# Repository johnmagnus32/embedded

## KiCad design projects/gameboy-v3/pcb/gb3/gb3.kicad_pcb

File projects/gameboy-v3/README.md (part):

# gameboy-v3 — Allwinner T113-S3 Linux handheld

**Status:** 🚧 Bring-up. Goal right now: **boot a Linux image on the
[t113-breakout](../t113-breakout) board and get a working serial console.**
Display, sound, and input come later, once Linux boots reliably.

**Build: complete (Steps 0–4 ✅).** All four artifacts + a flashable SD image
(`build/output/gameboy-v3-sd.img`) build reproducibly via `make image` through the
shared engine [`forge/`](../../forge/) (see the [boot matrix](#boot-matrix--interchangeable-components--silicon-results)
for the provider matrix). **Runs on real T113 silicon** — both the custom and
all-OSS stacks boot to an interactive shell (flashing: [first boot](#flashing--first-boot-generic--local-bench)).

## Contents

This is the single doc for the product. Major sections:

- **Overview & build** — [what this is](#what-this-is) · [boot chain](#boot-chain-phase-1-everything-on-microsd) · [build plan (Steps 0–4)](#build-plan--build-it-by-hand-once-then-buildroot) · [UART console](#uart-console) · [both cores (SMP)](#both-cores-smp) · [references](#references)
- **[Boot matrix](#boot-matrix--interchangeable-components--silicon-results)** — the provider-interchange matrix + on-silicon results (formerly BOOT-MATRIX.md).
- **[SPI-NOR layout](#spi-nor-layout--the-loader-contract)** — the loader contract: NOR offsets, GV3NOR1 table, DRAM load addrs (formerly NOR-LAYOUT.md).
- **[Flashing & first boot](#flashing--first-boot-generic--local-bench)** — dd a card, wire the console, expected boot, troubleshooting (formerly FLASH.md).
- **[Remote rig](#remote-bring-up-rig-ssh-driven-nuc)** — the SSH/NUC bring-up runbook: power-cycle, UART capture, FEL (formerly REMOTE-RIG.md).
- **[ILI9341 LCD](#ili9341-spi-lcd-later-phase)** — the SPI display peripheral (formerly LCD-ILI9341.md).

## What this is

The third iteration of the handheld. Where v1 was bare-metal STM32 and v2 was
STM32 + iCE40 FPGA, **v3 moves to a full Linux SBC**: the dual-core ARM
Cortex-A7 **Allwinner T113-S3** (with 128 MB in-package DDR3) running mainline
Linux. Game logic, display, and audio all run as Linux userspace/kernel on the
one SoC — no separate CPU/PPU split.

For Phase 1 the **whole boot image lives on the microSD card** (SPI-NOR left
blank) so the dev loop is just "reflash the card." See
[Boot chain](#boot-chain-phase-1-everything-on-microsd) below.

For bring-up, the SoC lives on the **t113-breakout** board (see
[../t113-breakout/README.md](../t113-breakout) — *note: that project currently
has `BOM.md` + `PINOUT.md`, not a README*). Peripherals (ILI9341 display,
audio, buttons) get wired to the breakout's headers **later**; this phase is
boot + console only.

## Phase 1 goal (current)

1. Build/obtain a bootable Linux image (SPL/U-Boot + kernel + rootfs) as a
   **single microSD image** — SPI-NOR left blank.
2. `dd` the image to a card and boot the T113-S3 on the breakout board from it.
3. Get a **UART serial console** at the login prompt.

Everything below the display/audio/input line is out of scope until this works.

## Boot chain (Phase 1: everything on microSD)

For bring-up the **entire boot image lives on the microSD card** and the
on-board SPI-NOR is left **blank**. This is the standard Allwinner sunxi
bring-up path and the simplest possible loop: build one image, `dd` it to the
card, boot.

```
BROM  →  microSD  →  SPL (boot0)  →  U-Boot  →  kernel + rootfs
         (SPI-NOR blank → BROM finds no valid boot header there and boots SD)
```

Why all-SD first:
- **One artifact, one reflash.** A single full-disk `.img` (SPL + U-Boot + boot
  partition + rootfs) is written with one `dd`. To change anything, re-`dd` the card.
- **Avoids the SPI-NOR chicken-and-egg.** Writing SPL/U-Boot to the W25Q128
  needs *either* FEL tooling (`xfel`) *or* an already-booted U-Boot — you can't
  "flash the chip" on a bare board without one of those. SD boot needs neither.
- **FEL over USB-C is still the backstop.** If an SD image is bad, the BROM
  drops to Allwinner FEL (USB boot) and the board is recoverable — unbrickable.

A blank (0xFF) SPI-NOR has no valid Allwinner eGON boot header, so the BROM
skips it and boots the SD. Nothing needs to be on SPI-NOR for this to work; the
PC4/PC5 BOOT-SEL straps are moot while the flash is empty.

### SD image layout (standard sunxi)

- **SPL (boot0)** at **8 KB offset** (sector 16).
- **U-Boot** right after — the combined `u-boot-sunxi-with-spl.bin` covers both
  in a single write at the 8 KB offset.
- **Partitions** start well past that (e.g. first partition at 1 MB / 16 MB):
  a boot partition (kernel + DTB + boot script) and an ext4 rootfs.

```bash
# Option A: write just the SPL+U-Boot blob to a raw card, partition the rest yourself
sudo dd if=u-boot-sunxi-with-spl.bin of=/dev/sdX bs=1024 seek=8 conv=fsync

# Option B: dd a full prebuilt disk image (SPL+U-Boot+boot+rootfs) — one shot
sudo dd if=t113-gameboy-v3.img of=/dev/sdX bs=4M conv=fsync status=progress
```

> **Migrate to SPI-NOR later.** Once the software stack is proven, SPL/U-Boot
> (or a full boot image) can move to the W25Q128 for a more product-like,
> SD-optional boot. Not needed now — SPI-NOR stays blank for Phase 1.

## Build plan — build it by hand once, then Buildroot

**Approach (optimizing for understanding):** build each layer of the boot chain
**by hand, in boot order**, so every handoff is something you configured and
watched happen over UART. *Then* adopt Buildroot to make it reproducible. This
is the standard Bootlin/embedded-Linux teaching order — the from-scratch pass
builds the mental model, Buildroot becomes the tool you graduate to (it's small
and transparent, so after the manual pass you recognize every piece it
automates). Yocto is deliberately skipped — right tool for production, wrong
first teacher.

We're **using a prebuilt toolchain** (not building our own — that's a separate
rabbit hole). Everything else we build.

**Reproducibility & structure (forge refactor):** the build is driven by the
shared engine [`forge/`](../../forge/) (at the repo root, reused by any product),
not per-product scripts. `make image` from here resolves this product's selection
([local.conf](local.conf)) + board inputs and orchestrates the generic build
backends in [`forge/engine/`](../../forge/engine/) (the idempotent fetch/build
recipes — the old `NN-*.sh`, now engine-owned). Pins split by tier:
- **Engine** ([`forge/engine/engine.mk`](../../forge/engine/engine.mk)) — the
  HOST-constrained cross-toolchain / arch pins (chosen by the build host, not this
  product); the build mechanism itself lives in [`forge/engine/run-recipe.sh`](../../forge/engine/run-recipe.sh).
- **Product** ([`versions.env`](versions.env)) — the OSS component pins (kernel /
  U-Boot / BusyBox tags + checksums), as data. Bump a version here.
- **Board** ([`boards/t113-gameboy/`](boards/t113-gameboy/)) — `board.conf`, the
  single board config (provider targets + defconfigs/board-DT/console + NOR/DRAM/SD
  layout), plus the `*.dtsi` overlays + `boot.cmd` + `genimage.cfg`.

All build inputs/outputs land in `build/` (git-ignored); `rm -rf build/` then
`make image` is the reproducibility test. Never a floating "latest" — bump a pin
deliberately.

**Target facts (all mainline, verified against U-Boot/kernel git):**
- T113-S3 = **32-bit ARMv7-A** dual Cortex-A7 → an **`armv7-eabihf` glibc**
  toolchain (NOT `arm-none-eabi`, which is bare-metal). We use Bootlin's
  prebuilt, whose actual prefix is **`arm-buildroot-linux-gnueabihf-`** (Bootlin
  builds it with Buildroot; still a standard armv7 hard-float glibc GCC).
- **No TF-A / BL31 needed.** BL31 is a 64-bit (ARMv8 EL3) component; the generic
  sunxi docs' BL31 step applies only to A64/H616-class parts. The T113 is
  ARMv7 with no EL3, so U-Boot builds standalone.
- **DDR3 init is fully upstreamed** — no vendor fork required. It lives in
  U-Boot SPL at `drivers/ram/sunxi/dram_sun20i_d1.c`; the 128 MB DDR3 timings
  are baked into the board defconfig.
- **Both Cortex-A7 cores come up** on mainline — via PSCI supplied by U-Boot, not
  a kernel SMP method. `MACH_SUN8I_R528` selects U-Boot's built-in ARMv7 PSCI
  monitor (`arch/arm/cpu/armv7/sunxi/psci.c`), which releases CPU1 from reset and
  patches `enable-method="psci"` + a `/psci` node into the kernel DTB at boot. So
  the kernel needs no `platsmp.c` change and no static DT edit. (Correcting an
  earlier note — see [Both cores (SMP)](#both-cores-smp).)

### Step 0 — Build environment (toolchain + host make) ✅ implemented

Prepares everything needed before building anything. `make toolchain` provisions the
base host-tool set through the host-package subsystem
(`host_provision make toolchain-glibc toolchain-musl gen_init_cpio`; see
docs/LINUX_HOST_PACKAGE_MODEL.md). It fetches + checksum-verifies + extracts **two**
pinned Bootlin cross toolchains and sanity-checks each emits 32-bit ARM, and ensures
**GNU Make ≥ 4.0** is available (the kernel requires it — see Step 2); it uses the
host's own make if new enough, otherwise builds a pinned one into `build/hostmake/`.

- **glibc toolchain** (`arm-buildroot-linux-gnueabihf-`) → U-Boot + kernel (they
  don't link a target libc, so libc choice is irrelevant there).
- **musl toolchain** (`arm-buildroot-linux-musleabihf-`) → the rootfs only.
  musl-static BusyBox is ~34% smaller than glibc-static and has a lighter Linux
  syscall surface — both a size win now and groundwork for a hand-written kernel.

```bash
make host-toolchain-gcc host-gen_init_cpio   # provision the cross toolchain + cpio writer (also built on demand by any `make image`)
```

- Pinned: `armv7-eabihf--glibc--stable-2021.11-1` (GCC 10.3.0), verified against
  Bootlin's published SHA256. The script **refuses to proceed on a checksum
  mismatch** — an unverified toolchain never enters the build.
- **Why not the newest toolchain?** This build host is **glibc 2.26**. Bootlin's
  2024+/2025 toolchains ship a binutils `ld` that needs GLIBC_2.27, so its `ld`
  won't run here — the build dies at the first *link* step (a compile-only check
  passes, so it surfaces mid-build, confusingly). 2021.11 gives GCC 10.3.0
  (satisfies U-Boot's host-gcc-≥10 requirement) with a `ld` needing only
  GLIBC_2.14. On a newer host you can bump the pin (PKG_VERSION/PKG_SHA256) in the
  `forge/hostpackages/toolchain-*` recipes (toolchain pins are engine-tier — host-constrained).
- Installs to `build/toolchain/`; `CROSS_COMPILE=arm-buildroot-linux-gnueabihf-`
  (Bootlin builds their toolchains with Buildroot, hence the `buildroot` triple).
- [`forge/engine/run-recipe.sh`](../../forge/engine/run-recipe.sh) loads the build env at
  every node, which scrubs PATH to the cross toolchain + make + the HOSTTOOLS allowlist — set once, per build.

### Step 1 — U-Boot (SPL + U-Boot proper) ✅ implemented

Clones mainline U-Boot at a pinned tag, applies our board's console + host-tool
config, overlays the control DTB, builds, and copies the artifact to `output/`:

```bash
make bootloader BOOTLOADER=uboot   # idempotent; runs providers/bootloader/uboot/build.sh
# → build/output/u-boot-sunxi-with-spl.bin  (SPL + U-Boot + DTB, one ~480K blob)
```

- **Pinned U-Boot v2026.04**, `mangopi_mq_r_defconfig` (`CONFIG_MACH_SUN8I_R528=y`;
  T113-S3 shares the R528 die). T113 support has been in mainline since v2024.01;
  there is no generic `sun20i`/`t113` defconfig.
- **No TF-A/BL31** — 32-bit ARMv7 has no EL3; `SUNXI_BL31_BASE=0` for R528, so the
  build emits no BL31/SCP warning. (The generic sunxi docs' BL31 step is 64-bit-only.)
- **Both Cortex-A7 cores come up** at runtime: `MACH_SUN8I_R528` selects U-Boot's
  built-in **ARMv7 PSCI** monitor, which powers on CPU1 and patches
  `enable-method="psci"` into the kernel DTB at boot. No kernel patch needed.
  (This corrects the earlier "single-core only" note — see [Both cores](#both-cores-smp).)
- DRAM timings are baked into the defconfig (`DRAM_CLK=792`, `DRAM_ZQ=8092667`,
  `TPR0/11/12/13`, `SUNXI_MINIMUM_DRAM_MB=128`); same in-package die as the MQ-R,
  so they should port unchanged — only re-tune if the board proves unstable.

**Console → UART0/PE2-PE3 (the [#1 trap](#uart-console)):** the script applies
**both** required changes and it's verified in the built DTB:
1. `CONFIG_CONS_INDEX=1` (defconfig) → SPL console pinmux to PE2/PE3.
2. `boards/t113-gameboy/uart0-console.dtsi` overlay (`#include`d into the board `.dts`) →
   sets `stdout-path=serial0`, `serial0=&uart0`, enables `&uart0` on a
   `uart0_pe_pins` (PE2/PE3) group, disables `&uart3`. Needed because U-Boot
   *proper* uses DM serial and reads the console from the DTB — `CONS_INDEX`
   alone gives a split-brain console (SPL on UART0, U-Boot proper back on UART3).

**Host-tool trims** (baked into the config fragment; this build host lacks the
libs and a sunxi image doesn't need them): `TOOLS_LIBCRYPTO=n` (host OpenSSL
1.0.2 too old for U-Boot's signing tools; no signing needed), `TOOLS_KWBIMAGE=n`
(Marvell, pulls in libcrypto), `TOOLS_MKEFICAPSULE=n` (needs gnutls headers).
The script also builds an isolated **python venv** (`build/pyenv/`) with
binman's deps (pyelftools/pyyaml/setuptools/importlib_resources) because the
Bootlin toolchain ships its own python3 that lacks them.

**Learning checkpoint:** `dd` this to a card (Step 4) with nothing else, power on,
and you should get the U-Boot prompt over UART. That alone proves BROM → SPL
(DRAM init) → U-Boot.

### Step 2 — Kernel + device tree ✅ implemented

Clones mainline Linux at a pinned LTS tag, builds `zImage` + the board DTB with
the UART0 console overlay, copies both to `output/`:

```bash
make kernel KERNEL=mainline        # idempotent; runs providers/kernel/mainline/build.sh
# → build/output/zImage  and  build/output/sun8i-t113s-mangopi-mq-r-t113.dtb
```

- **Pinned Linux v6.12.95** (LTS; T113 board DTS landed v6.4, settled into the
  `allwinner/` subdir at v6.5), `sunxi_defconfig`. Enables the essentials as `=y`:
  `SERIAL_8250_DW` (UART), `MMC_SUNXI` (SD), the D1/T113 CCU + pinctrl.
- **DTB:** `sun8i-t113s-mangopi-mq-r-t113.dtb` (SoC dtsi cross-includes the RISC-V
  D1's sun20i dtsi files — expected; same die).
- **Console → UART0:** the script `#include`s the **same `boards/t113-gameboy/uart0-console.dtsi`**
  overlay used for U-Boot (the kernel DTS is structurally identical). Verified in
  the built DTB: `stdout-path=serial0`, uart0 okay on PE2/PE3, uart3 disabled.
  With `serial0=&uart0`, Linux names uart0 **ttyS0** → the kernel cmdline console
  is `console=ttyS0,115200` (set in the boot script in Step 4, not the DTB).
- **Both cores:** the kernel DTS's `cpu@1` has no `enable-method` — that's fine;
  U-Boot's PSCI patches it in at boot (see [Both cores](#both-cores-smp)).

**Host workarounds** (this build host is old): the kernel needs **GNU Make ≥ 4.0**,
which **Step 0** provides (uses the host's if new enough, else builds a pinned
Make 4.4.1 into `build/hostmake/`) — this step just verifies it. And
`CONFIG_GCC_PLUGINS` is disabled here because the host lacks `gmp.h` (a hardening
feature, not needed to reach a console).

**Learning checkpoint:** boot `zImage` + DTB from U-Boot and watch kernel log
spew over UART. First rootfs iteration is easiest over **NFS** (no reflash per
build) before committing to an SD rootfs.

### Step 3 — Root filesystem (static BusyBox initramfs) ✅ implemented

The highest teaching-per-effort step: a static BusyBox + a tiny `/init`, packed
as a `cpio.gz` initramfs — the simplest thing that boots straight to a shell
(no root partition, no `root=`; U-Boot loads kernel + DTB + initramfs together).

```bash
make rootfs KERNEL=mainline LIBC=musl PACKAGES=busybox   # runs forge/steps/rootfs/build.sh
# → build/output/initramfs.cpio.gz   (~792K: musl-static busybox + 401 applets)
```

- **Pinned BusyBox 1.36.1** (last upstream "stable"-labeled release), SHA256-verified.
- **Built with the musl toolchain** (`CROSS_COMPILE`), not glibc: the
  static binary is 1.38 MB vs 2.08 MB, so the initramfs is **792 KB vs 1.15 MB
  (31% smaller)**. Selected via BusyBox's `CONFIG_CROSS_COMPILER_PREFIX` **and**
  `CROSS_COMPILE=` on both the build and `make install` lines — the install step
  re-checks deps and would otherwise silently rebuild with the glibc env compiler.
- **Static build:** `make defconfig`, then `CONFIG_STATIC=y` + `CONFIG_TC=n` via a
  scripted `.config` edit + `make oldconfig`. `CONFIG_TC=n` avoids the `tc.c`
  `TCA_CBQ_MAX` break (kernel headers ≥ 6.8 removed it; unfixed upstream) and
  isn't needed for a minimal rootfs anyway.
- **`/init` is PID 1** — a SINGLE portable [overlay/init.sh](overlay/init.sh)
  shipped for EVERY rootfs provider (PID-1 policy is the product's, not the
  provider's). Written in the shell subset both our gv3 shell and busybox parse:
  best-effort mounts `/proc`, `/sys`, devtmpfs `/dev` (real on mainline; kernel
  no-op success on the custom stack), a static banner, then `exec /bin/sh`. If
  PID 1 ever exits the kernel panics — so it hands off to a shell that stays up.
- **Packaged with the kernel's `gen_init_cpio`** (reused from Step 2's tree): it
  emits a root-owned cpio and creates `/dev/console` (char 5,1) **without needing
  root** — that node must exist in the initramfs or PID 1 gets no stdin/out/err.

Verified by listing the built cpio (`cpio -itv`): `/init` 0755 root, `bin/busybox`
static ARM, `/dev/console` present, 401 applet symlinks → `/bin/busybox`.

> **Learning note:** to *see* the "clicks" for real, temporarily remove `/init`
> from the image and boot — the kernel panics with "No init found." Add it back
> and the shell appears. That failure→fix is the whole lesson in how userspace
> starts.

**Then graduate to Buildroot** for a reproducible rootfs (and, if you like, to
drive the U-Boot + kernel builds too): start from the community
`utuM/Buildroot-T113-S3` (board `mq-dual`) and adjust the kernel/U-Boot DT for
our console. After this manual pass, its generated `.config` and `output/build/`
tree will read like a checklist of things you already understand.

### Step 4 — Assemble the SD image ✅ implemented

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
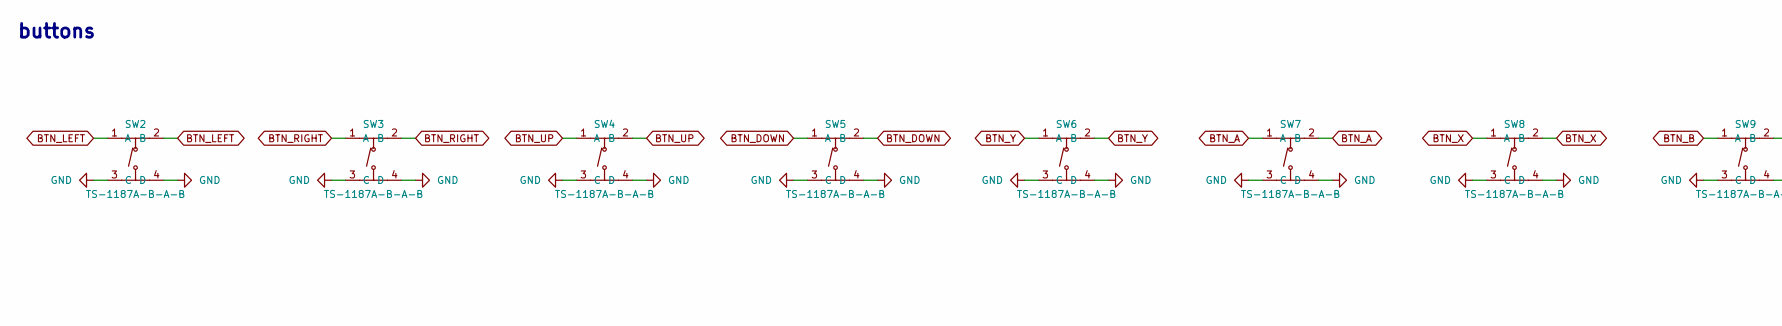
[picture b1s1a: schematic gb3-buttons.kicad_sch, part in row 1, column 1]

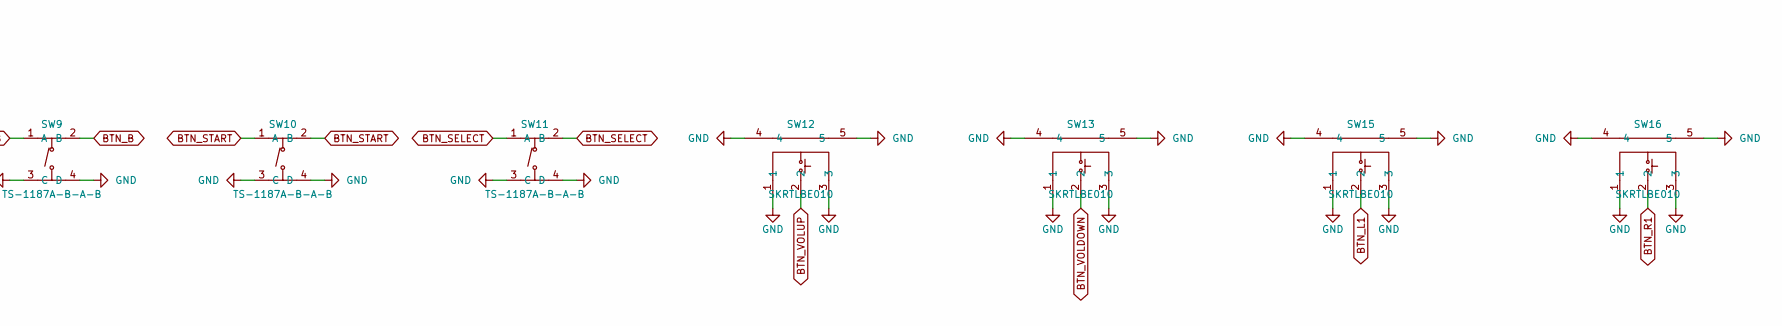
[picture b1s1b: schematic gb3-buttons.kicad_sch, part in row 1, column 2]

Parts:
SW2, SW3, SW4, SW5, SW6, SW7, SW8, SW9, SW10, SW11: TS-1187A-B-A-B; SW-SMD_4P-L5.1-W5.1-P3.70-LS6.5-TL_H1.5; LCSC C318884
SW12, SW13, SW15, SW16: SKRTLBE010; KEY-SMD_SKRTLAE010-1; LCSC C127481

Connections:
BTN_A: SW7.1 (A), SW7.2 (B); also elsewhere on the board
BTN_B: SW9.1 (A), SW9.2 (B); also elsewhere on the board
BTN_DOWN: SW5.1 (A), SW5.2 (B); also elsewhere on the board
BTN_L1: SW15.2; also elsewhere on the board
BTN_LEFT: SW2.1 (A), SW2.2 (B); also elsewhere on the board
BTN_R1: SW16.2; also elsewhere on the board
BTN_RIGHT: SW3.1 (A), SW3.2 (B); also elsewhere on the board
BTN_SELECT: SW11.1 (A), SW11.2 (B); also elsewhere on the board
BTN_START: SW10.1 (A), SW10.2 (B); also elsewhere on the board
BTN_UP: SW4.1 (A), SW4.2 (B); also elsewhere on the board
BTN_VOLDOWN: SW13.2; also elsewhere on the board
BTN_VOLUP: SW12.2; also elsewhere on the board
BTN_X: SW8.1 (A), SW8.2 (B); also elsewhere on the board
BTN_Y: SW6.1 (A), SW6.2 (B); also elsewhere on the board
GND: SW2.3 (C), SW2.4 (D), SW3.3 (C), SW3.4 (D), SW4.3 (C), SW4.4 (D), SW5.3 (C), SW5.4 (D), SW6.3 (C), SW6.4 (D), SW7.3 (C), SW7.4 (D), SW8.3 (C), SW8.4 (D), SW9.3 (C), SW9.4 (D), SW10.3 (C), SW10.4 (D), SW11.3 (C), SW11.4 (D), SW12.1, SW12.3, SW12.4, SW12.5, SW13.1, SW13.3, SW13.4, SW13.5, SW15.1, SW15.3, SW15.4, SW15.5, SW16.1, SW16.3, SW16.4, SW16.5; also elsewhere on the board

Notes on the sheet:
buttons

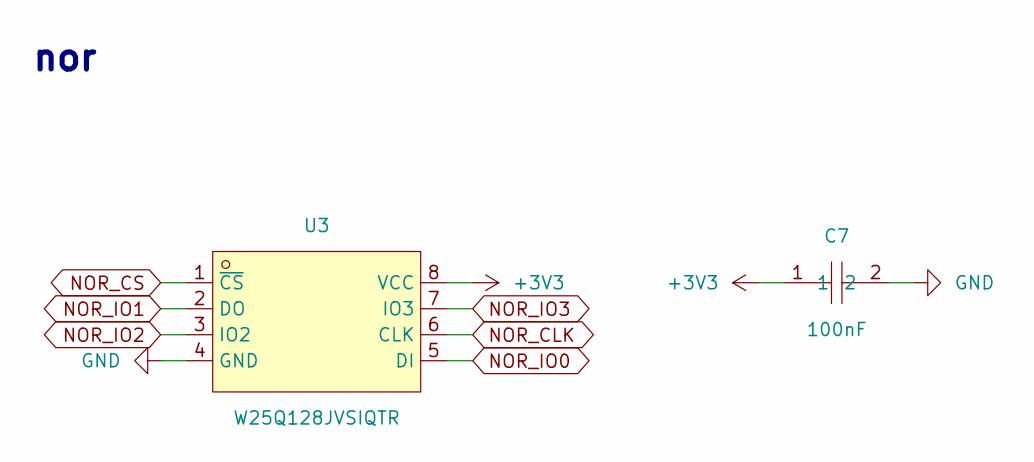
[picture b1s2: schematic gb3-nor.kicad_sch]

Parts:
C7: 100nF; C0603; LCSC C14663
U3: W25Q128JVSIQTR; SOIC-8_L5.3-W5.3-P1.27-LS8.0-BL; LCSC C97521

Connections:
+3V3: C7.1, U3.8 (VCC); also elsewhere on the board
GND: C7.2, U3.4 (GND); also elsewhere on the board
NOR_CLK: U3.6 (CLK); also elsewhere on the board
NOR_CS: U3.1 (~CS); also elsewhere on the board
NOR_IO0: U3.5 (DI); also elsewhere on the board
NOR_IO1: U3.2 (DO); also elsewhere on the board
NOR_IO2: U3.3 (IO2); also elsewhere on the board
NOR_IO3: U3.7 (IO3); also elsewhere on the board

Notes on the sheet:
nor

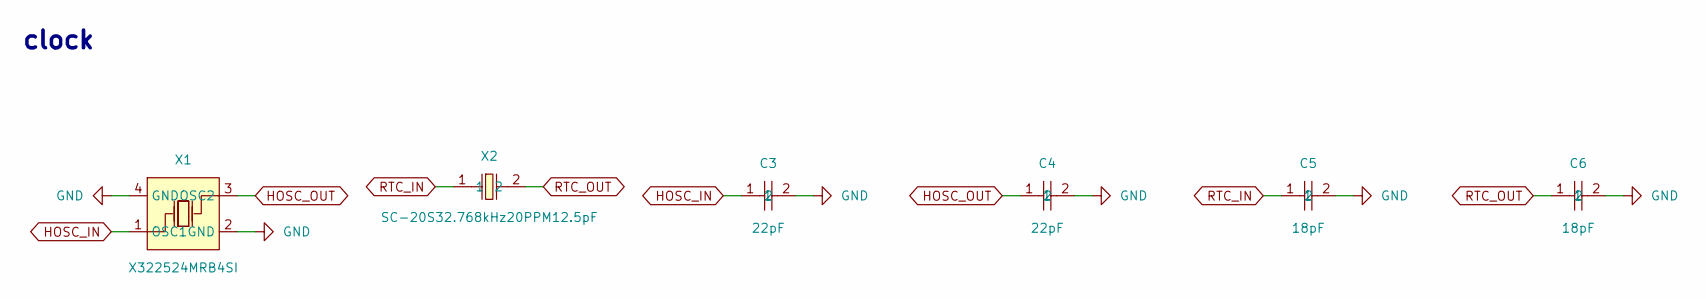
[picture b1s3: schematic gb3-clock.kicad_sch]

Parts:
C3, C4: 22pF; C0402; LCSC C1555
C5, C6: 18pF; C0402; LCSC C1549
X1: X322524MRB4SI; CRYSTAL-SMD_4P-L3.2-W2.5-BL-2; LCSC C70571
X2: SC-20S32.768kHz20PPM12.5pF; OSC-SMD_L2.0-W1.2; LCSC C97607

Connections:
GND: C3.2, C4.2, C5.2, C6.2, X1.2 (GND), X1.4 (GND); also elsewhere on the board
HOSC_IN: C3.1, X1.1 (OSC1); also elsewhere on the board
HOSC_OUT: C4.1, X1.3 (OSC2); also elsewhere on the board
RTC_IN: C5.1, X2.1; also elsewhere on the board
RTC_OUT: C6.1, X2.2; also elsewhere on the board

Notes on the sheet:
clock

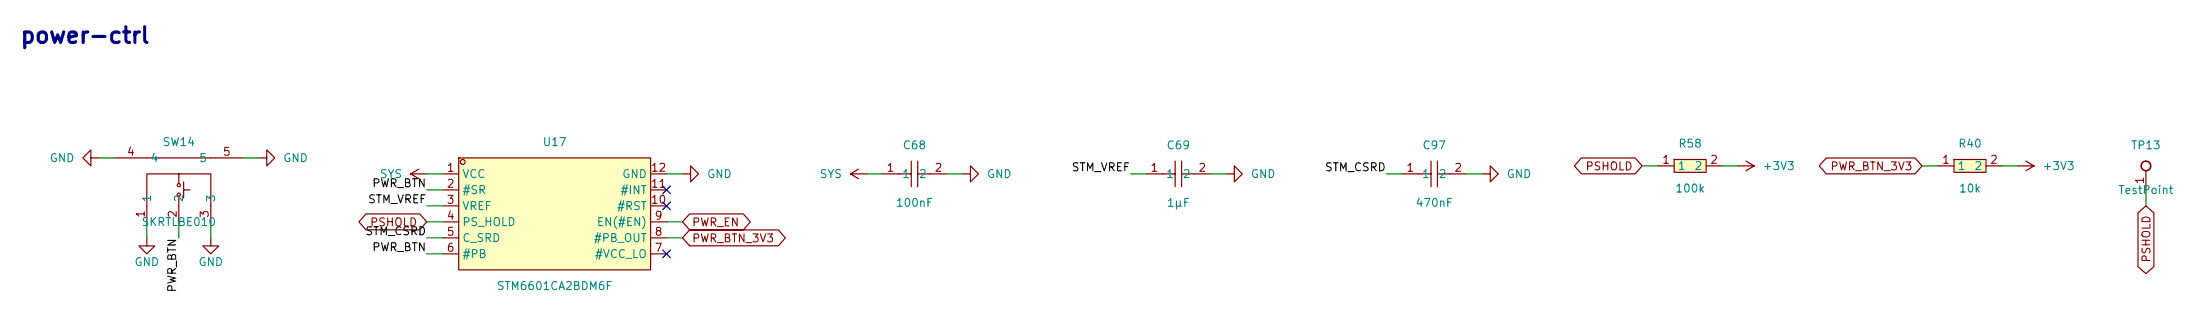
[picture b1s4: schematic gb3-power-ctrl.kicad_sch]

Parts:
C68: 100nF; C0603; LCSC C14663
C69: 1µF; C0603; LCSC C15849
C97: 470nF; C0603; LCSC C1623
R40: 10k; R0603; LCSC C99198
R58: 100k; R0603; LCSC C14675
SW14: SKRTLBE010; KEY-SMD_SKRTLAE010-1; LCSC C127481
TP13: TestPoint; TestPoint_Pad_D1.5mm
U17: STM6601CA2BDM6F; TDFN-12_L3.0-W2.0-P0.50-BL; LCSC C109022

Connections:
+3V3: R40.2, R58.2; also elsewhere on the board
/power-ctrl/PWR_BTN: SW14.2, U17.2 (#SR), U17.6 (#PB)
/power-ctrl/STM_CSRD: C97.1, U17.5 (C_SRD)
/power-ctrl/STM_VREF: C69.1, U17.3 (VREF)
GND: C68.2, C69.2, C97.2, SW14.1, SW14.3, SW14.4, SW14.5, U17.12 (GND); also elsewhere on the board
PSHOLD: R58.1, TP13.1, U17.4 (PS_HOLD); also elsewhere on the board
PWR_BTN_3V3: R40.1, U17.8 (#PB_OUT); also elsewhere on the board
PWR_EN: U17.9 (EN(#EN)); also elsewhere on the board
SYS: C68.1, U17.1 (VCC); also elsewhere on the board

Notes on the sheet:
power-ctrl

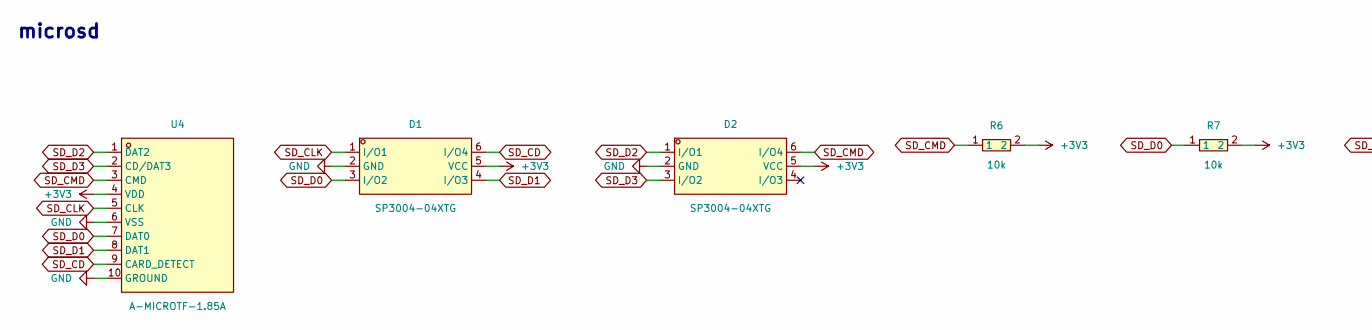
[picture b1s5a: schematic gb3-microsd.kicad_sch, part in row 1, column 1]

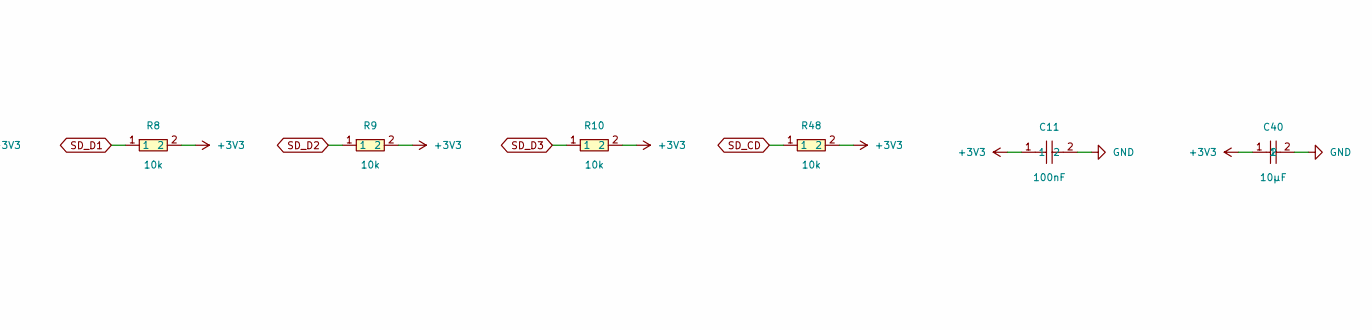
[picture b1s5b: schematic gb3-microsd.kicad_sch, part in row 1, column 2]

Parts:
C11: 100nF; C0603; LCSC C14663
C40: 10µF; C0805; LCSC C1713
D1, D2: SP3004-04XTG; SOT-563_L1.6-W1.2-P0.50-LS1.6-BR; LCSC C207280
R6, R7, R8, R9, R10, R48: 10k; R0603; LCSC C99198
U4: A-MICROTF-1.85A; TF-SMD_A-MICROTF-1.85A; LCSC C22467599

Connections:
+3V3: C11.1, C40.1, D1.5 (VCC), D2.5 (VCC), R6.2, R7.2, R8.2, R9.2, R10.2, R48.2, U4.4 (VDD); also elsewhere on the board
GND: C11.2, C40.2, D1.2 (GND), D2.2 (GND), U4.6 (VSS), U4.10 (GROUND); also elsewhere on the board
SD_CD: D1.6 (I/O4), R48.1, U4.9 (CARD_DETECT); also elsewhere on the board
SD_CLK: D1.1 (I/O1), U4.5 (CLK); also elsewhere on the board
SD_CMD: D2.6 (I/O4), R6.1, U4.3 (CMD); also elsewhere on the board
SD_D0: D1.3 (I/O2), R7.1, U4.7 (DAT0); also elsewhere on the board
SD_D1: D1.4 (I/O3), R8.1, U4.8 (DAT1); also elsewhere on the board
SD_D2: D2.1 (I/O1), R9.1, U4.1 (DAT2); also elsewhere on the board
SD_D3: D2.3 (I/O2), R10.1, U4.2 (CD/DAT3); also elsewhere on the board

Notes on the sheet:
microsd

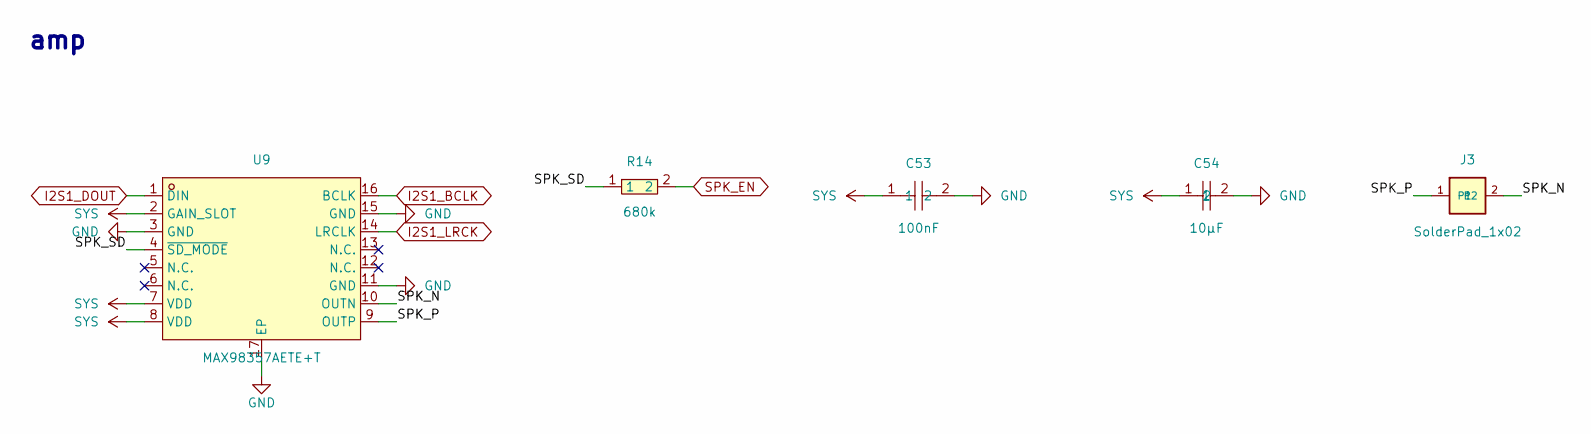
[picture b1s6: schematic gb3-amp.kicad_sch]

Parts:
C53: 100nF; C0603; LCSC C14663
C54: 10µF; C0805; LCSC C17024
J3: SolderPad_1x02; SolderPad_1x02_SMD
R14: 680k; R0603; LCSC C140074
U9: MAX98357AETE+T; TQFN-16_L3.0-W3.0-P0.50-BL-EP1.5; LCSC C910544

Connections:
/amp/SPK_N: J3.2, U9.10 (OUTN)
/amp/SPK_P: J3.1, U9.9 (OUTP)
/amp/SPK_SD: R14.1, U9.4 (~SD_MODE)
GND: C53.2, C54.2, U9.3 (GND), U9.11 (GND), U9.15 (GND), U9.17 (EP); also elsewhere on the board
I2S1_BCLK: U9.16 (BCLK); also elsewhere on the board
I2S1_DOUT: U9.1 (DIN); also elsewhere on the board
I2S1_LRCK: U9.14 (LRCLK); also elsewhere on the board
SPK_EN: R14.2; also elsewhere on the board
SYS: C53.1, C54.1, U9.2 (GAIN_SLOT), U9.7 (VDD), U9.8 (VDD); also elsewhere on the board

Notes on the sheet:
amp

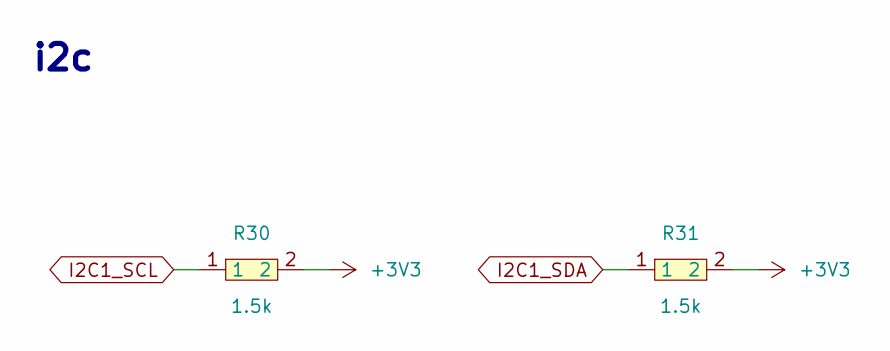
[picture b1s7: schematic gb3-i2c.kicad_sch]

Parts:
R30, R31: 1.5k; R0603; LCSC C22843

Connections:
+3V3: R30.2, R31.2; also elsewhere on the board
I2C1_SCL: R30.1; also elsewhere on the board
I2C1_SDA: R31.1; also elsewhere on the board

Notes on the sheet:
i2c

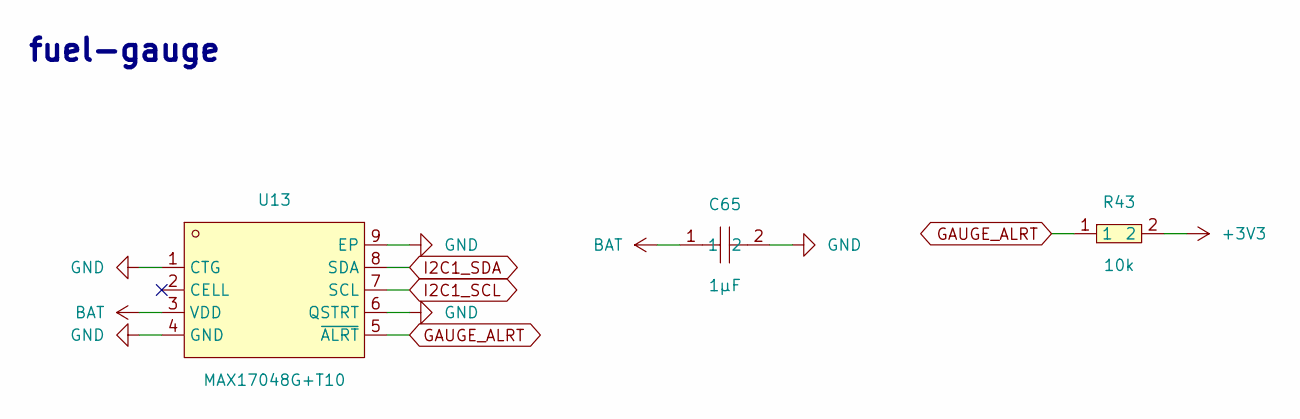
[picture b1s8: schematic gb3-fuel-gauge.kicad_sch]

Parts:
C65: 1µF; C0603; LCSC C15849
R43: 10k; R0603; LCSC C99198
U13: MAX17048G+T10; TDFN-8_L2.0-W2.0-P0.50-BL-EP1.2; LCSC C2682616

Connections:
+3V3: R43.2; also elsewhere on the board
BAT: C65.1, U13.3 (VDD); also elsewhere on the board
GAUGE_ALRT: R43.1, U13.5 (~ALRT); also elsewhere on the board
GND: C65.2, U13.1 (CTG), U13.4 (GND), U13.6 (QSTRT), U13.9 (EP); also elsewhere on the board
I2C1_SCL: U13.7 (SCL); also elsewhere on the board
I2C1_SDA: U13.8 (SDA); also elsewhere on the board

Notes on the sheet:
fuel-gauge

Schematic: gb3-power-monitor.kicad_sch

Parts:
C66: 100nF; C0603; LCSC C14663
R27: 10mΩ; R2512; LCSC C393072
TP6: TestPoint; TestPoint_Pad_D1.5mm
U15: INA226AIDGSR; MSOP-10_L3.0-W3.0-P0.50-LS5.0-BL; LCSC C49851

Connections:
+3V3: C66.1, U15.6 (VS+); also elsewhere on the board
GND: C66.2, U15.1 (A1), U15.2 (A0), U15.7 (GND); also elsewhere on the board
I2C1_SCL: U15.5 (SCL); also elsewhere on the board
I2C1_SDA: U15.4 (SDA); also elsewhere on the board
SYS: R27.2, TP6.1, U15.8 (VBUS), U15.9 (VIN-); also elsewhere on the board
SYS_SRC: R27.1, U15.10 (VIN+); also elsewhere on the board

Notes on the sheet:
power-monitor

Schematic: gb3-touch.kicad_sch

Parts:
FPC1: 1.0K-1.5-6PWB; FPC-SMD_6P-P1.00_HDGC_1.0K-1.5-6PWB; LCSC C2919568

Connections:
+3V3: FPC1.6; also elsewhere on the board
GND: FPC1.5, FPC1.7, FPC1.8; also elsewhere on the board
I2C1_SCL: FPC1.4; also elsewhere on the board
I2C1_SDA: FPC1.3; also elsewhere on the board
TOUCH_INT: FPC1.2; also elsewhere on the board
TOUCH_RST: FPC1.1; also elsewhere on the board

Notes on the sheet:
touch

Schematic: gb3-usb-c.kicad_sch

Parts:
C93: 100nF; C0603; LCSC C14663
D4: USBLC6-2SC6; SOT-23-6_L2.9-W1.6-P0.95-LS2.8-BL; LCSC C7519
R52, R53: 5.1k; R0603; LCSC C105580
R56, R57: 200k; R0603; LCSC C25811
USBC1: TYPE-C-31-M-12; USB-C_SMD-TYPE-C-31-M-12_1; LCSC C165948

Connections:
+5V: C93.1, D4.5, USBC1.A4B9 (VBUS), USBC1.B4A9 (VBUS); also elsewhere on the board
/usb-c/USBC_CC1: R52.1, R56.1, USBC1.A5 (CC1)
/usb-c/USBC_CC2: R53.1, R57.1, USBC1.B5 (CC2)
GND: C93.2, D4.2, R52.2, R53.2, USBC1.1 (EH), USBC1.2 (EH), USBC1.3 (EH), USBC1.4 (EH), USBC1.A1B12 (GND), USBC1.B1A12 (GND); also elsewhere on the board
USBC_CC_SENSE: R56.2, R57.2; also elsewhere on the board
USB_D+: D4.3, D4.4, USBC1.A6 (DP1), USBC1.B6 (DP2); also elsewhere on the board
USB_D-: D4.1, D4.6, USBC1.A7 (DN1), USBC1.B7 (DN2); also elsewhere on the board

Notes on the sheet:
usb-c

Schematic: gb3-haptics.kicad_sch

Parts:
C50: 1µF; C0603; LCSC C15849
C51: 100nF; C0603; LCSC C14663
C52: 10µF; C0805; LCSC C1713
J2: SolderPad_1x02; SolderPad_1x02_SMD
U8: DRV2605LDGSR; VSSOP-10_L3.0-W3.0-P0.50-LS4.9-BL; LCSC C527464

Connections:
+3V3: C51.1, C52.1, U8.5 (EN), U8.6 (VDD/NC), U8.10 (VDD); also elsewhere on the board
/haptics/HAP_REG: C50.1, U8.1 (REG)
/haptics/LRA_N: J2.2, U8.9 (OUT-)
/haptics/LRA_P: J2.1, U8.7 (OUT+)
GND: C50.2, C51.2, C52.2, U8.4 (IN/TRIG), U8.8 (GND); also elsewhere on the board
I2C1_SCL: U8.2 (SCL); also elsewhere on the board
I2C1_SDA: U8.3 (SDA); also elsewhere on the board

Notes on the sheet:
haptics

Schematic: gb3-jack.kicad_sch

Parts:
Audio1: PJ-327C-4A; AUDIO-SMD_PJ-327C-4A; LCSC C145813
R49: 10k; R0603; LCSC C99198

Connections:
/jack/JACK_SW: Audio1.4, R49.1
GND: Audio1.1; also elsewhere on the board
HP_L: Audio1.2; also elsewhere on the board
HP_R: Audio1.3; also elsewhere on the board
JACK_DET: R49.2; also elsewhere on the board

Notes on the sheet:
jack

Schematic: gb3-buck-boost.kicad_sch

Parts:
C59: 100nF; C0603; LCSC C14663
C60, C61: 10µF; C0805; LCSC C1713
C62, C63, C64: 22µF; C0805; LCSC C45783
L3: 1.5µH; IND-SMD_L5.4-W5.2; LCSC C408407
R22, R23: 0Ω; R0603; LCSC C21189
TP7: TestPoint; TestPoint_Pad_D1.5mm
U12: TPS63021DSJR; VSON-14_L4.0-W3.0-P0.50-BL-EP_TI_DSJ; LCSC C202140

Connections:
+3V3: C62.1, C63.1, C64.1, R22.2, TP7.1, U12.4 (VOUT), U12.5 (VOUT); also elsewhere on the board
/buck-boost/BB_FB: R22.1, U12.3 (FB)
/buck-boost/BB_L1: L3.1, U12.8 (L1), U12.9 (L1)
/buck-boost/BB_L2: L3.2, U12.6 (L2), U12.7 (L2)
/buck-boost/BB_PSYNC: R23.1, U12.13 (PS/SYNC)
GND: C59.2, C60.2, C61.2, C62.2, C63.2, C64.2, R23.2, U12.2 (GND), U12.15 (PGND); also elsewhere on the board
PWR_EN: U12.12 (EN); also elsewhere on the board
SYS: C59.1, C60.1, C61.1, U12.1 (VINA), U12.10 (VIN), U12.11 (VIN); also elsewhere on the board

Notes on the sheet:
buck-boost

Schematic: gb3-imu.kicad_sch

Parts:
C48, C49: 100nF; C0603; LCSC C14663
R13: 10k; R0603; LCSC C99198
R41, R42: 1.5k; R0603; LCSC C22843
U7: LSM6DSOXTR; LGA-14L_L3.0-W2.5-P0.50-TL; LCSC C481766

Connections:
+3V3: C48.1, C49.1, R41.2, R42.2, U7.5 (VDDIO), U7.8 (VDD), U7.12 (CS); also elsewhere on the board
GND: C48.2, C49.2, R13.2, U7.1 (SDO/SA0), U7.2 (SDX), U7.3 (SCX), U7.6 (GND), U7.7 (GND); also elsewhere on the board
I2C2_SCL: R41.1, U7.13 (SCL); also elsewhere on the board
I2C2_SDA: R42.1, U7.14 (SDA); also elsewhere on the board
IMU_INT1: R13.1, U7.4 (INT1); also elsewhere on the board
IMU_INT2: U7.9 (INT2); also elsewhere on the board

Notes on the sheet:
imu

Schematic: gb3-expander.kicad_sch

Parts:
C67: 100nF; C0603; LCSC C14663
R29: 10k; R0603; LCSC C99198
U16: PCA9555PWR; TSSOP-24_L7.8-W4.4-P0.65-LS6.4-BL; LCSC C2864778

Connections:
+3V3: C67.1, R29.2, U16.24 (VCC); also elsewhere on the board
BTN_A: U16.7 (P03); also elsewhere on the board
BTN_B: U16.10 (P06); also elsewhere on the board
BTN_DOWN: U16.13 (P10); also elsewhere on the board
BTN_L1: U16.18 (P15); also elsewhere on the board
BTN_LEFT: U16.14 (P11); also elsewhere on the board
BTN_R1: U16.4 (P00); also elsewhere on the board
BTN_RIGHT: U16.15 (P12); also elsewhere on the board
BTN_SELECT: U16.9 (P05); also elsewhere on the board
BTN_START: U16.17 (P14); also elsewhere on the board
BTN_UP: U16.16 (P13); also elsewhere on the board
BTN_VOLDOWN: U16.6 (P02); also elsewhere on the board
BTN_VOLUP: U16.5 (P01); also elsewhere on the board
BTN_X: U16.8 (P04); also elsewhere on the board
BTN_Y: U16.11 (P07); also elsewhere on the board
EXP_INT: R29.1, U16.1 (~INT); also elsewhere on the board
GND: C67.2, U16.2 (A1), U16.3 (A2), U16.12 (GND), U16.21 (A0); also elsewhere on the board
I2C1_SCL: U16.22 (SCL); also elsewhere on the board
I2C1_SDA: U16.23 (SDA); also elsewhere on the board

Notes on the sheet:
expander

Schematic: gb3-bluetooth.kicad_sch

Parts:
C70, C73: 4.7µF; C0603; LCSC C109456
C71, C72: 100nF; C0603; LCSC C14663
U18: BT830-SA-01-T_R; XCVR_BT830-SA-01-T_R

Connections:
+3V3: C71.1, C72.1, C73.1, U18.1 (VDD_PADS), U18.9 (VREG_IN_HV); also elsewhere on the board
/bluetooth/BT_VREG18: C70.1, U18.10 (VREG_OUT_HV)
BT_EN_RST: U18.8 (VREG_EN_~RST); also elsewhere on the board
GND: C70.2, C71.2, C72.2, C73.2, U18.2 (GND), U18.11 (GND), U18.12 (GND), U18.13 (GND), U18.14 (GND), U18.15 (GND), U18.16 (GND), U18.18 (GND), U18.23 (GND), U18.28 (SPI_~PCM_SEL), U18.30 (GND); also elsewhere on the board
UART3_CTS: U18.4 (~UART_RTS); also elsewhere on the board
UART3_RTS: U18.6 (~UART_CTS); also elsewhere on the board
UART3_RX: U18.5 (UART_TX); also elsewhere on the board
UART3_TX: U18.7 (UART_RX); also elsewhere on the board

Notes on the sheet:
bluetooth

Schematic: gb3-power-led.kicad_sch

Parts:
R12: 510Ω; R0603; LCSC C23193
U5: 19-213SYGC/S454/5T; LED0603-RD; LCSC C2986057

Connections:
+3V3: R12.1; also elsewhere on the board
/power-led/PWR_LED_A: R12.2, U5.2 (+)
GND: U5.1 (-); also elsewhere on the board

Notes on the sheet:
power-led

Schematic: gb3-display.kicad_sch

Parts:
C95, C96: 100nF; C0603; LCSC C14663
P1: FPCConnector 40PIN 0.5MM; FPC-SMD_40P-P0.50_FG-H2.0-40P; LCSC C9160
R39: 10k; R0603; LCSC C99198

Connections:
+3V3: C95.1, C96.1, P1.4, R39.2; also elsewhere on the board
BL_LED_N: P1.1; also elsewhere on the board
BL_LED_P: P1.2; also elsewhere on the board
GND: C95.2, C96.2, P1.3, P1.5, P1.6, P1.13, P1.14, P1.21, P1.22, P1.29, P1.36, P1.41, P1.42; also elsewhere on the board
PANEL_DISP: P1.31, R39.1; also elsewhere on the board
RGB_B2: P1.23; also elsewhere on the board
RGB_B3: P1.24; also elsewhere on the board
RGB_B4: P1.25; also elsewhere on the board
RGB_B5: P1.26; also elsewhere on the board
RGB_B6: P1.27; also elsewhere on the board
RGB_B7: P1.28; also elsewhere on the board
RGB_DCLK: P1.30; also elsewhere on the board
RGB_DE: P1.34; also elsewhere on the board
RGB_G2: P1.15; also elsewhere on the board
RGB_G3: P1.16; also elsewhere on the board
RGB_G4: P1.17; also elsewhere on the board
RGB_G5: P1.18; also elsewhere on the board
RGB_G6: P1.19; also elsewhere on the board
RGB_G7: P1.20; also elsewhere on the board
RGB_HSYNC: P1.32; also elsewhere on the board
RGB_R2: P1.7; also elsewhere on the board
RGB_R3: P1.8; also elsewhere on the board
RGB_R4: P1.9; also elsewhere on the board
RGB_R5: P1.10; also elsewhere on the board
RGB_R6: P1.11; also elsewhere on the board
RGB_R7: P1.12; also elsewhere on the board
RGB_VSYNC: P1.33; also elsewhere on the board

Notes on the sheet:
display

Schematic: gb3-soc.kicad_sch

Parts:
C8, C9, C10, C12, C13, C14, C15, C16, C17, C18, C19, C20, C21, C22, C23, C24, C25, C26, C27, C28, C29, C30, C31, C94: 100nF; C0603; LCSC C14663
C35, C36, C37, C38, C39: 10µF; C0805; LCSC C1713
C41, C42, C43, C44: 4.7µF; C0603; LCSC C109456
C92: 2.2µF; C0805; LCSC C125847
R5: 240Ω; R0603; LCSC C23350
R11: 10k; R0603; LCSC C99198
R45, R46: 510Ω; R0603; LCSC C23193
R50: 33Ω; R0603; LCSC C23140
SW1: TS-1187A-B-A-B; SW-SMD_4P-L5.1-W5.1-P3.70-LS6.5-TL_H1.5; LCSC C318884
TP1, TP2, TP3, TP9, TP10: TestPoint; TestPoint_Pad_D1.5mm
U1: T113-S3_C5197687; LQFP-128_L14.0-W14.0-P0.40-LS16.0-BL-EP5.6; LCSC C5197687

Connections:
+0V9: C14.1, C15.1, C16.1, C17.1, C18.1, C39.1, U1.46 (VDD-SYS0), U1.51 (VDD-SYS1), U1.81 (VDD-SYS2), U1.116 (VDD-CORE0), U1.117 (VDD-CORE1); also elsewhere on the board
+3V3: C8.1, C9.1, C10.1, C12.1, C29.1, C30.1, C36.1, C37.1, C38.1, C41.1, C43.1, C44.1, U1.29 (LDO-IN), U1.34 (VCC-PE), U1.66 (VCC-PD), U1.77 (VCC-TVOUT), U1.83 (VCC-IO), U1.128 (VCC-PG); also elsewhere on the board
/soc/DDR_ZQ: R5.1, U1.47 (DZQ)
/soc/I2S1_MCLK: U1.6 (PG11)
/soc/LCD0_CLK: R50.1, U1.75 (PD18)
/soc/RESET: C31.1, R11.1, SW1.1 (A), SW1.2 (B), U1.27 (RESET)
/soc/UART0_RX: R46.1, U1.33 (PE3)
/soc/UART0_RX_PAD: R46.2, TP2.1
/soc/UART0_TX: R45.1, U1.35 (PE2)
/soc/UART0_TX_PAD: R45.2, TP1.1
AVCC: C19.1, C92.1, U1.89 (AVCC)
BL_CTRL: U1.37 (PE10); also elsewhere on the board
BT_EN_RST: U1.84 (PB4); also elsewhere on the board
CHG_FAST: U1.79 (PB7); also elsewhere on the board
CHG_PGOOD: U1.80 (PB6); also elsewhere on the board
DAC_XSMT: U1.85 (PB3); also elsewhere on the board
EXP_INT: U1.40 (PE7); also elsewhere on the board
GAUGE_ALRT: U1.82 (PB5); also elsewhere on the board
GND: C8.2, C9.2, C10.2, C12.2, C13.2, C14.2, C15.2, C16.2, C17.2, C18.2, C19.2, C20.2, C21.2, C22.2, C23.2, C24.2, C25.2, C26.2, C27.2, C28.2, C29.2, C30.2, C31.2, C35.2, C36.2, C37.2, C38.2, C39.2, C41.2, C42.2, C43.2, C44.2, C92.2, C94.2, R5.2, SW1.3 (C), SW1.4 (D), TP3.1, U1.91 (AGND), U1.129 (EPAD); also elsewhere on the board
HOSC_IN: U1.23 (DXIN); also elsewhere on the board
HOSC_OUT: U1.22 (DXOUT); also elsewhere on the board
HPVCC: C20.1, U1.97 (HPVCC)
HP_EN: U1.86 (PB2); also elsewhere on the board
I2C1_SCL: U1.3 (PG8); also elsewhere on the board
I2C1_SDA: U1.4 (PG9); also elsewhere on the board
I2C2_SCL: U1.43 (PE4); also elsewhere on the board
I2C2_SDA: U1.42 (PE5); also elsewhere on the board
I2S1_BCLK: U1.125 (PG13); also elsewhere on the board
I2S1_DOUT: U1.127 (PG15); also elsewhere on the board
I2S1_LRCK: U1.124 (PG12); also elsewhere on the board
IMU_INT1: U1.45 (PE1); also elsewhere on the board
IMU_INT2: U1.44 (PE0); also elsewhere on the board
JACK_DET: U1.126 (PG14); also elsewhere on the board
LDOA: C13.1, C23.1, C24.1, C25.1, C42.1, R11.2, TP9.1, U1.20 (VCC-PLL), U1.26 (VCC-RTC), U1.28 (LDOA-OUT), U1.50 (VDD18-DRAM), U1.65 (VCC-LVDS), U1.107 (VCC-TVIN)
LDOB: C26.1, C27.1, C28.1, C35.1, TP10.1, U1.30 (LDOB-OUT), U1.48 (VCC-DRAM0), U1.49 (VCC-DRAM1)
NOR_CLK: U1.19 (PC2); also elsewhere on the board
NOR_CS: U1.18 (PC3); also elsewhere on the board
NOR_IO0: U1.17 (PC4); also elsewhere on the board
NOR_IO1: U1.16 (PC5); also elsewhere on the board
NOR_IO2: U1.15 (PC6); also elsewhere on the board
NOR_IO3: U1.14 (PC7); also elsewhere on the board
PANEL_DISP: U1.52 (PD22); also elsewhere on the board
PSHOLD: U1.36 (PE11); also elsewhere on the board
PWR_BTN_3V3: U1.31 (PE13); also elsewhere on the board
RGB_B2: U1.55 (PD0); also elsewhere on the board
RGB_B3: U1.56 (PD1); also elsewhere on the board
RGB_B4: U1.57 (PD2); also elsewhere on the board
RGB_B5: U1.58 (PD3); also elsewhere on the board
RGB_B6: U1.59 (PD4); also elsewhere on the board
RGB_B7: U1.60 (PD5); also elsewhere on the board
RGB_DCLK: R50.2; also elsewhere on the board
RGB_DE: U1.76 (PD19); also elsewhere on the board
RGB_G2: U1.61 (PD6); also elsewhere on the board
RGB_G3: U1.62 (PD7); also elsewhere on the board
RGB_G4: U1.63 (PD8); also elsewhere on the board
RGB_G5: U1.64 (PD9); also elsewhere on the board
RGB_G6: U1.67 (PD10); also elsewhere on the board
RGB_G7: U1.68 (PD11); also elsewhere on the board
RGB_HSYNC: U1.54 (PD20); also elsewhere on the board
RGB_R2: U1.70 (PD12); also elsewhere on the board
RGB_R3: U1.69 (PD13); also elsewhere on the board
RGB_R4: U1.71 (PD14); also elsewhere on the board
RGB_R5: U1.72 (PD15); also elsewhere on the board
RGB_R6: U1.73 (PD16); also elsewhere on the board
RGB_R7: U1.74 (PD17); also elsewhere on the board
RGB_VSYNC: U1.53 (PD21); also elsewhere on the board
RTC_IN: U1.25 (X32KIN); also elsewhere on the board
RTC_OUT: U1.24 (X32KOUT); also elsewhere on the board
SD_CD: U1.5 (PG10); also elsewhere on the board
SD_CLK: U1.9 (PF2); also elsewhere on the board
SD_CMD: U1.10 (PF3); also elsewhere on the board
SD_D0: U1.8 (PF1); also elsewhere on the board
SD_D1: U1.7 (PF0); also elsewhere on the board
SD_D2: U1.12 (PF5); also elsewhere on the board
SD_D3: U1.11 (PF4); also elsewhere on the board
SPK_EN: U1.41 (PE6); also elsewhere on the board
TOUCH_INT: U1.39 (PE8); also elsewhere on the board
TOUCH_RST: U1.38 (PE9); also elsewhere on the board
UART3_CTS: U1.121 (PG3); also elsewhere on the board
UART3_RTS: U1.119 (PG2); also elsewhere on the board
UART3_RX: U1.118 (PG1); also elsewhere on the board
UART3_TX: U1.120 (PG0); also elsewhere on the board
USBC_CC_SENSE: C94.1, U1.101 (GPADC0); also elsewhere on the board
USB_D+: U1.115 (USB0-DP); also elsewhere on the board
USB_D-: U1.114 (USB0-DM); also elsewhere on the board
VRA1: C21.1, U1.92 (VRA1)
VRA2: C22.1, U1.90 (VRA2)

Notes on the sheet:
soc

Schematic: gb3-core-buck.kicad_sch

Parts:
C1: 10pF; C0402; LCSC C32949
C2: 100nF; C0603; LCSC C14663
C33, C34: 10µF; C0805; LCSC C1713
L1: 2.2µH; IND-SMD_L4.0-W4.0_LQH44PN2R2MP0L; LCSC C135262
R2: 150k; R0603; LCSC C22807
R3: 75k; R0603; LCSC C23242
R4: 100k; R0603; LCSC C14675
TP8: TestPoint; TestPoint_Pad_D1.5mm
U2: FP6161KR-LF-ADJ; SOT-23-5_L3.0-W1.7-P0.95-LS2.8-BL; LCSC C77234

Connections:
+0V9: C1.1, C34.1, L1.2, R3.1, TP8.1; also elsewhere on the board
+3V3: C33.1, R4.1, U2.4 (VIN); also elsewhere on the board
/core-buck/CORE_FB: C1.2, R2.1, R3.2, U2.5 (FB/VOUT)
/core-buck/CORE_RUN: C2.1, R4.2, U2.1 (RUN)
/core-buck/CORE_SW: L1.1, U2.3 (SW)
GND: C2.2, C33.2, C34.2, R2.2, U2.2 (GND); also elsewhere on the board

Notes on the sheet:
core-buck

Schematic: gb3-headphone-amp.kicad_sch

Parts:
C85, C86, C87, C88: 1µF; C0603; LCSC C15849
C89, C90: 2.2µF; C0805; LCSC C125847
C91: 100nF; C0603; LCSC C14663
R37: 100k; R0603; LCSC C14675
U20: TPA6132A2RTER; WQFN-16_L3.0-W3.0-P0.50-TL-EP1.6; LCSC C69901

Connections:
+3V3: C90.1, C91.1, U20.14 (VDD); also elsewhere on the board
/headphone-amp/AMP_INL: C86.2, U20.4 (INR-)
/headphone-amp/AMP_INR: C85.2, U20.1 (INL-)
/headphone-amp/TPA_CPN: C87.2, U20.9 (CPN)
/headphone-amp/TPA_CPP: C87.1, U20.11 (CPP)
/headphone-amp/TPA_HPVDD: C89.1, U20.12 (HPVDD)
/headphone-amp/TPA_HPVSS: C88.1, U20.8 (HPVSS)
DAC_OUTL_F: C86.1; also elsewhere on the board
DAC_OUTR_F: C85.1; also elsewhere on the board
GND: C88.2, C89.2, C90.2, C91.2, R37.2, U20.2 (INL+), U20.3 (INR+), U20.6 (G0), U20.7 (G1), U20.10 (PGND), U20.15 (SGND), U20.17 (EP); also elsewhere on the board
HP_EN: R37.1, U20.13 (EN); also elsewhere on the board
HP_L: U20.5 (OUTR); also elsewhere on the board
HP_R: U20.16 (OUTL); also elsewhere on the board

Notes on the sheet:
headphone-amp

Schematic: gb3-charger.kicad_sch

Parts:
C55: 4.7µF; C0603; LCSC C19666
C56, C57: 10µF; C0805; LCSC C1713
CN1: S2B-PH-SM4-TB; CONN-SMD_P2.00_S2B-PH-SM4-TB-LF-SN; LCSC C295747
Q1: 2N7002; SOT-23-3_L2.9-W1.3-P1.90-LS2.4-BR; LCSC C8545
R15: 2k; R0603; LCSC C22975
R16: 3.6k; R0603; LCSC C22980
R17: 10k; R0603; LCSC C2892547
R18: 0Ω; R0603; LCSC C21189
R26: 1k; R0603; LCSC C21190
R28, R55: 10k; R0603; LCSC C99198
R47: 68k; R0603; LCSC C23231
R54: 1.8k; R0603; LCSC C4177
TP4, TP5, TP12: TestPoint; TestPoint_Pad_D1.5mm
U10: BQ24073RGTR; QFN-16_L3.0-W3.0-P0.50-TL-EP1.7; LCSC C15220
U14: 19-213SYGC/S454/5T; LED0603-RD; LCSC C2986057

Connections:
+3V3: R28.2; also elsewhere on the board
+5V: C55.1, TP4.1, U10.13 (IN); also elsewhere on the board
/charger/CHG_EN2: R18.1, U10.5 (EN2)
/charger/CHG_ILIM: R16.1, R54.1, U10.12 (ILIM)
/charger/CHG_ILIM_SW: Q1.3 (D), R54.2
/charger/CHG_ISET: R15.1, U10.16 (ISET)
/charger/CHG_LED_A: R26.2, U14.2 (+)
/charger/CHG_LED_K: U10.9 (~CHG), U14.1 (-)
/charger/CHG_TMR: R47.1, U10.14 (TMR)
/charger/CHG_TS: R17.1, U10.1 (TS)
BAT: C57.1, CN1.1, TP5.1, U10.2 (BAT), U10.3 (BAT); also elsewhere on the board
CHG_FAST: Q1.1 (G), R55.1; also elsewhere on the board
CHG_PGOOD: R28.1, U10.7 (~PGOOD); also elsewhere on the board
GND: C55.2, C56.2, C57.2, CN1.2, CN1.3, CN1.4, Q1.2 (S), R15.2, R16.2, R17.2, R47.2, R55.2, TP12.1, U10.4 (~CE), U10.6 (EN1), U10.8 (VSS), U10.15 (TD), U10.17 (EP); also elsewhere on the board
SYS_SRC: C56.1, R18.2, R26.1, U10.10 (OUT), U10.11 (OUT); also elsewhere on the board

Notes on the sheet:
charger

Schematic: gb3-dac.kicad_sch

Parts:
C74, C75, C76, C77: 100nF; C0603; LCSC C14663
C78, C79, C80: 10µF; C0805; LCSC C1713
C81, C82: 2.2µF; C0805; LCSC C125847
C83, C84: 2.2nF; C0603; LCSC C33353
R32, R33, R34: 0Ω; R0603; LCSC C21189
R35, R36: 470Ω; R0603; LCSC C23179
R44: 10k; R0603; LCSC C99198
U19: PCM5102APWR; TSSOP-20_L6.5-W4.4-P0.65-LS6.4-BL; LCSC C107671

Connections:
+3V3: C74.1, C75.1, C76.1, C78.1, C79.1, C80.1, U19.1 (CPVDD), U19.8 (AVDD), U19.20 (DVDD); also elsewhere on the board
/dac/DAC_BCK: R32.2, U19.13 (BCK)
/dac/DAC_DIN: R34.2, U19.14 (DIN)
/dac/DAC_LRCK: R33.2, U19.15 (LRCK)
/dac/DAC_OUTL: R36.1, U19.6 (OUTL)
/dac/DAC_OUTR: R35.1, U19.7 (OUTR)
/dac/PCM_CAPM: C81.2, U19.4 (CAPM)
/dac/PCM_CAPP: C81.1, U19.2 (CAPP)
/dac/PCM_LDOO: C77.1, U19.18 (LDOO)
/dac/PCM_VNEG: C82.1, U19.5 (VNEG)
DAC_OUTL_F: C84.1, R36.2; also elsewhere on the board
DAC_OUTR_F: C83.1, R35.2; also elsewhere on the board
DAC_XSMT: R44.1, U19.17 (XSMT); also elsewhere on the board
GND: C74.2, C75.2, C76.2, C77.2, C78.2, C79.2, C80.2, C82.2, C83.2, C84.2, R44.2, U19.3 (CPGND), U19.9 (AGND), U19.10 (DEMP), U19.11 (FLT), U19.12 (SCK), U19.16 (FMT), U19.19 (DGND); also elsewhere on the board
I2S1_BCLK: R32.1; also elsewhere on the board
I2S1_DOUT: R34.1; also elsewhere on the board
I2S1_LRCK: R33.1; also elsewhere on the board

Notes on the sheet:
dac
